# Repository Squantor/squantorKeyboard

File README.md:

# My own keyboard stuff
This repository contains my experiments on creating my own keyboard electronics and software.
## Structure
* [electronics](electronics/README.md) contains keyboard circuits boards and possible controllers.
* [software](software/README.md) contains all the software used in the project. This can be embedded, PC/smartphone or test scripts, anything a computer can execute resides here.
* [mechanical](mechanical/README.md) contains all the CAD drawings, mostly 3d printable objects.
* [documentation](documentation/index.md) contains all project documentation, logs, research, papers, datasheets and more.
## Cloning
This repository makes extensive use of submodules, use ```git clone --recurse-submodules https://github.com/Squantor/squantorKeyboard.git``` to clone everything in one go.
# TODOs
Open tasks

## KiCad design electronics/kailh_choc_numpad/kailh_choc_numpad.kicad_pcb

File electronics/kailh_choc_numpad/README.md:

# Kailh Choc numpad tryout
Trying out kailh choc numpad with using 2 port expanders
# HSI (Hardware Software Interface)
* 16 bit port expander at address 0x??
	* Pin 0: Row 0 drive
	* Pin 1: Row 1 drive
	* Pin 2: Row 2 drive
	* Pin 3: Row 2 drive
	* Pin 4: Row 2 drive
	* Pin 8: Column 0 LED drive, pulled up by 100K
	* Pin 9: Column 1 LED drive, pulled up by 100K
	* Pin 10: Column 2 LED drive, pulled up by 100K
	* Pin 11: Column 3 LED drive, pulled up by 100K
* 8 bit port expander at address 0x??
	* Pin 0: Column 0 switch sense, pulled up by 4.7K
	* Pin 1: Column 1 switch sense, pulled up by 4.7K
	* Pin 2: Column 2 switch sense, pulled up by 4.7K
	* Pin 3: Column 3 switch sense, pulled up by 4.7K
Matrix switches and definitions:
TODO
## TODO's
Still some things need to be done:
* schematic entry
* expand HSI 
* PCB layout
* Review with one night in between
* Produce at [OSHPARK](https://oshpark.com/)
* Assemble
* Test & characterise
* update Readme.md with pictures and BOM
## BOM
* TODO: 16 bit port expander
* TODO: 8 bit port expander
* TODO: Kailh choc 1350 switches
* TODO: keycaps from kailhua for kailh choc keys

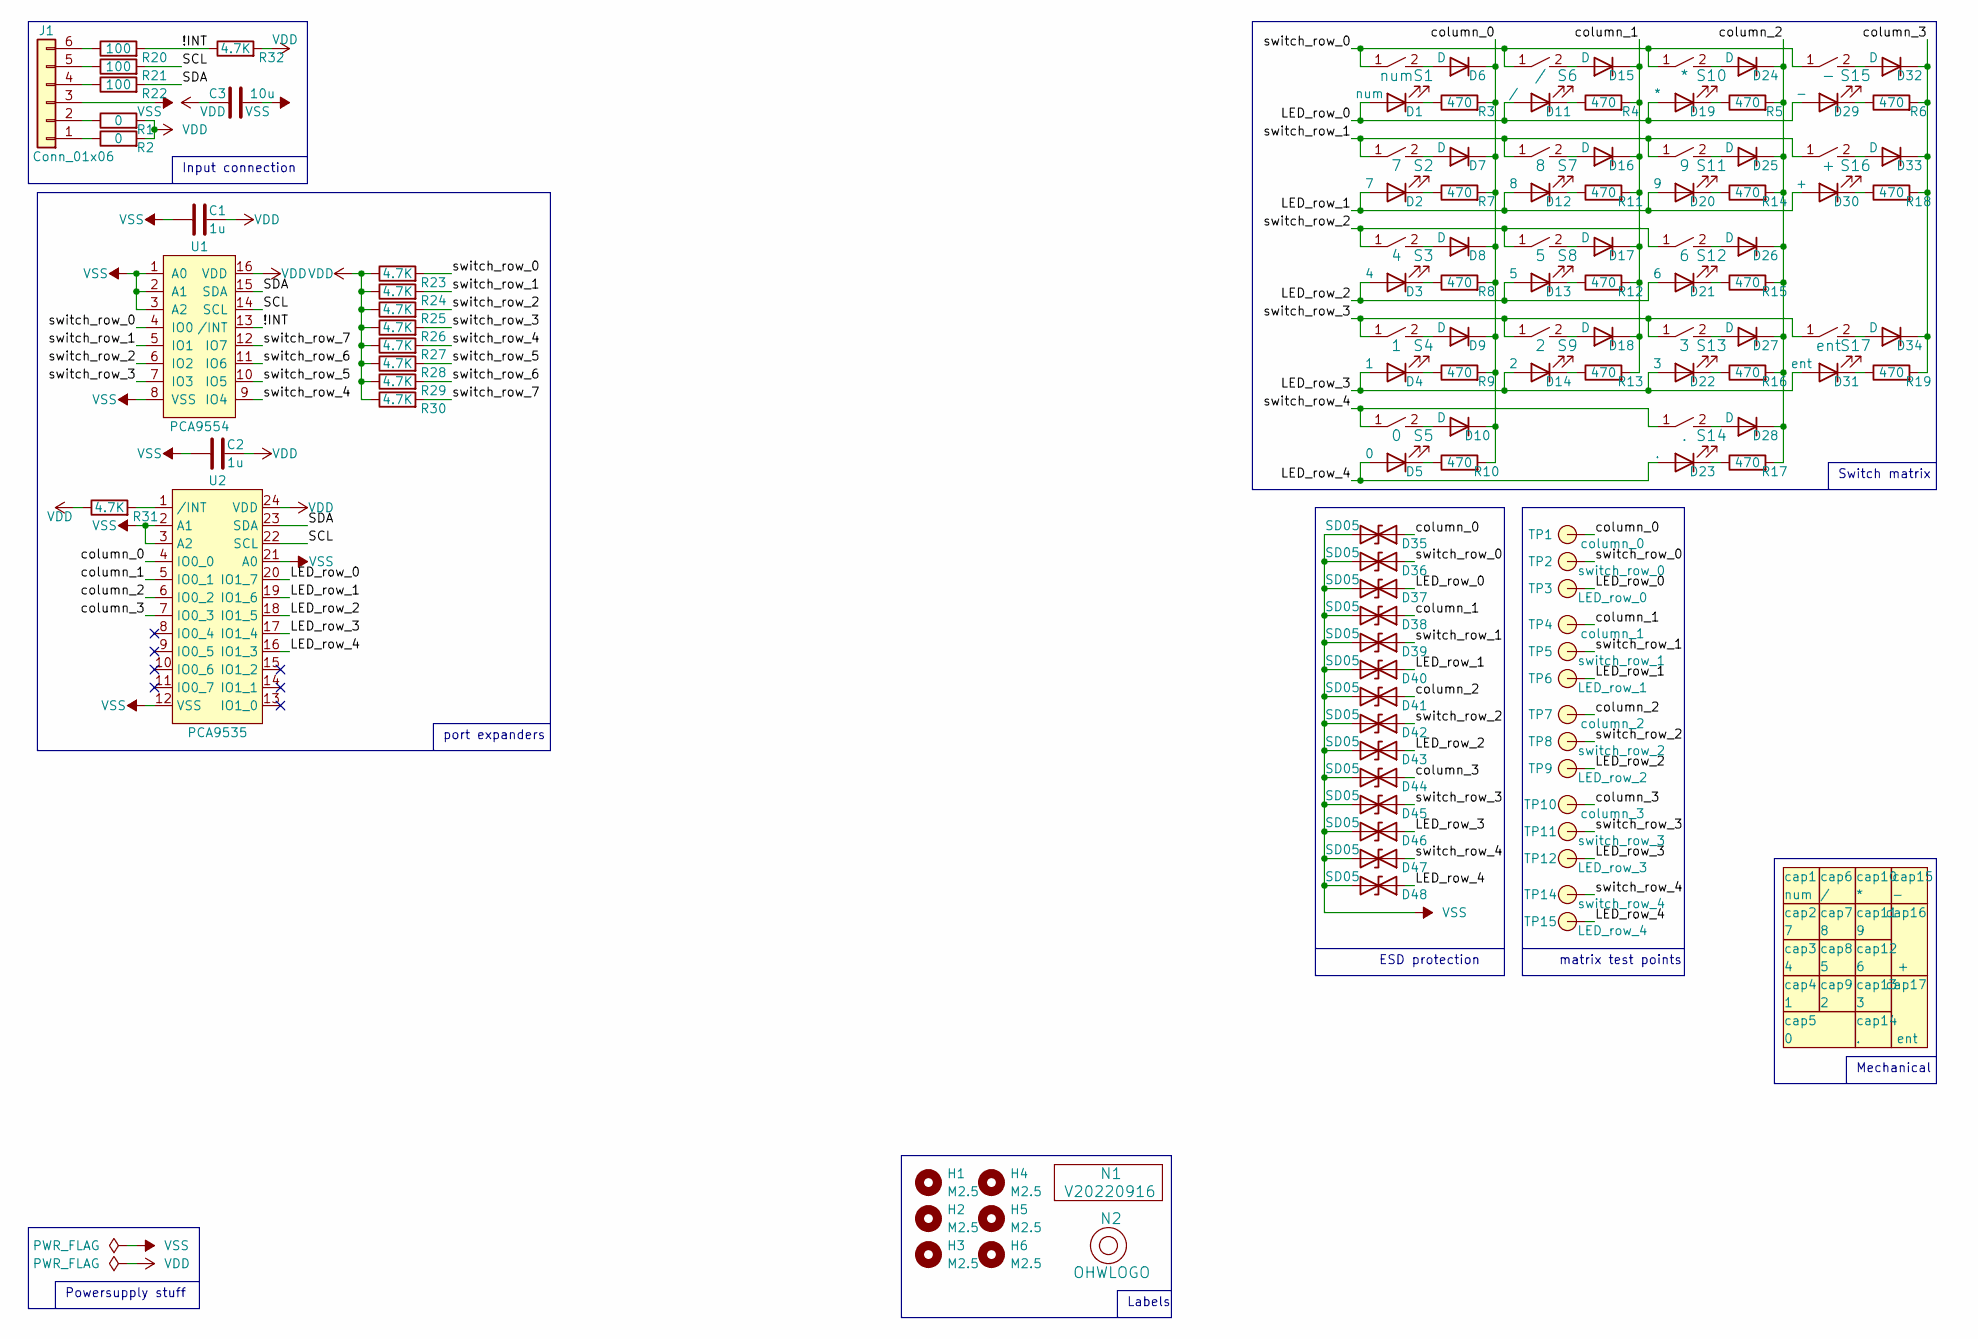
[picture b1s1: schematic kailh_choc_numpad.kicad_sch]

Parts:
C1, C2: 1u; C_0603
C3: 10u; C_0805
D1: num; LED_1208_0603
D2: 7; LED_1208_0603
D3: 4; LED_1208_0603
D4: 1; LED_1208_0603
D5: 0; LED_1208_0603
D6, D7, D8, D9, D10, D15, D16, D17, D18, D24, D25, D26, D27, D28, D32, D33, D34: D; SOD-523_hand
D11: /; LED_1208_0603
D12: 8; LED_1208_0603
D13: 5; LED_1208_0603
D14: 2; LED_1208_0603
D19: *; LED_1208_0603
D20: 9; LED_1208_0603
D21: 6; LED_1208_0603
D22: 3; LED_1208_0603
D23: .; LED_1208_0603
D29: -; LED_1208_0603
D30: +; LED_1208_0603
D31: ent; LED_1208_0603
D35, D36, D37, D38, D39, D40, D41, D42, D43, D44, D45, D46, D47, D48: SD05; D_SOD-323
H1, H2, H3, H4, H5, H6: M2.5; MountingHole_2.7mm_M2.5
J1: Conn_01x06; JST_PH_S6B-PH-K_1x06_P2.00mm_Horizontal
N1: V20220916; Label_Generic
N2: OHWLOGO; OSHW-Symbol_8.9x8mm_SilkScreen
R1, R2: 0; R_0603_hand
R3, R4, R5, R6, R7, R8, R9, R10, R11, R12, R13, R14, R15, R16, R17, R18, R19: 470; R_0603_hand
R20, R21, R22: 100; R_0603_hand
R23, R24, R25, R26, R27, R28, R29, R30, R31, R32: 4.7K; R_0603_hand
S1: num; KAILH_choc_LED
S2: 7; KAILH_choc_LED
S3: 4; KAILH_choc_LED
S4: 1; KAILH_choc_LED
S5: 0; KAILH_choc_LED
S6: /; KAILH_choc_LED
S7: 8; KAILH_choc_LED
S8: 5; KAILH_choc_LED
S9: 2; KAILH_choc_LED
S10: *; KAILH_choc_LED
S11: 9; KAILH_choc_LED
S12: 6; KAILH_choc_LED
S13: 3; KAILH_choc_LED
S14: .; KAILH_choc_LED
S15: -; KAILH_choc_LED
S16: +; KAILH_choc_LED
S17: ent; KAILH_choc_LED
TP1: column_0; TestPoint_hole_H05R10
TP2: switch_row_0; TestPoint_hole_H05R10
TP3: LED_row_0; TestPoint_hole_H05R10
TP4: column_1; TestPoint_hole_H05R10
TP5: switch_row_1; TestPoint_hole_H05R10
TP6: LED_row_1; TestPoint_hole_H05R10
TP7: column_2; TestPoint_hole_H05R10
TP8: switch_row_2; TestPoint_hole_H05R10
TP9: LED_row_2; TestPoint_hole_H05R10
TP10: column_3; TestPoint_hole_H05R10
TP11: switch_row_3; TestPoint_hole_H05R10
TP12: LED_row_3; TestPoint_hole_H05R10
TP14: switch_row_4; TestPoint_hole_H05R10
TP15: LED_row_4; TestPoint_hole_H05R10
U1: PCA9554; SOT403-1-NXP
U2: PCA9535; SOT355-1-NXP
cap1: num; KAILH_choc_keycap_1
cap2: 7; KAILH_choc_keycap_1
cap3: 4; KAILH_choc_keycap_1
cap4: 1; KAILH_choc_keycap_1
cap5: 0; KAILH_choc_keycap_2_horizontal
cap6: /; KAILH_choc_keycap_1
cap7: 8; KAILH_choc_keycap_1
cap8: 5; KAILH_choc_keycap_1
cap9: 2; KAILH_choc_keycap_1
cap10: *; KAILH_choc_keycap_1
cap11: 9; KAILH_choc_keycap_1
cap12: 6; KAILH_choc_keycap_1
cap13: 3; KAILH_choc_keycap_1
cap14: .; KAILH_choc_keycap_1
cap15: -; KAILH_choc_keycap_1
cap16: +; KAILH_choc_keycap_2_vertical
cap17: ent; KAILH_choc_keycap_2_vertical

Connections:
/!INT: R20.2, R32.1, U1.13 (/INT)
/LED_row_0: D1.2 (A), D11.2 (A), D19.2 (A), D29.2 (A), D37.1 (A1), TP3.1, U2.20 (IO1_7)
/LED_row_1: D2.2 (A), D12.2 (A), D20.2 (A), D30.2 (A), D40.1 (A1), TP6.1, U2.19 (IO1_6)
/LED_row_2: D3.2 (A), D13.2 (A), D21.2 (A), D43.1 (A1), TP9.1, U2.18 (IO1_5)
/LED_row_3: D4.2 (A), D14.2 (A), D22.2 (A), D31.2 (A), D46.1 (A1), TP12.1, U2.17 (IO1_4)
/LED_row_4: D5.2 (A), D23.2 (A), D48.1 (A1), TP15.1, U2.16 (IO1_3)
/SCL: R21.2, U1.14 (SCL), U2.22 (SCL)
/SDA: R22.2, U1.15 (SDA), U2.23 (SDA)
/column_0: D6.1 (K), D7.1 (K), D8.1 (K), D9.1 (K), D10.1 (K), D35.1 (A1), R3.2, R7.2, R8.2, R9.2, R10.2, TP1.1, U2.4 (IO0_0)
/column_1: D15.1 (K), D16.1 (K), D17.1 (K), D18.1 (K), D38.1 (A1), R4.2, R11.2, R12.2, R13.2, TP4.1, U2.5 (IO0_1)
/column_2: D24.1 (K), D25.1 (K), D26.1 (K), D27.1 (K), D28.1 (K), D41.1 (A1), R5.2, R14.2, R15.2, R16.2, R17.2, TP7.1, U2.6 (IO0_2)
/column_3: D32.1 (K), D33.1 (K), D34.1 (K), D44.1 (A1), R6.2, R18.2, R19.2, TP10.1, U2.7 (IO0_3)
/switch_row_0: D36.1 (A1), R23.2, S1.1, S6.1, S10.1, S15.1, TP2.1, U1.4 (IO0)
/switch_row_1: D39.1 (A1), R24.2, S2.1, S7.1, S11.1, S16.1, TP5.1, U1.5 (IO1)
/switch_row_2: D42.1 (A1), R25.2, S3.1, S8.1, S12.1, TP8.1, U1.6 (IO2)
/switch_row_3: D45.1 (A1), R26.2, S4.1, S9.1, S13.1, S17.1, TP11.1, U1.7 (IO3)
/switch_row_4: D47.1 (A1), R27.2, S5.1, S14.1, TP14.1, U1.9 (IO4)
/switch_row_5: R28.2, U1.10 (IO5)
/switch_row_6: R29.2, U1.11 (IO6)
/switch_row_7: R30.2, U1.12 (IO7)
unnamed: D1.1 (K), R3.1
unnamed: D2.1 (K), R7.1
unnamed: D3.1 (K), R8.1
unnamed: D4.1 (K), R9.1
unnamed: D5.1 (K), R10.1
unnamed: D6.2 (A), S1.2
unnamed: D7.2 (A), S2.2
unnamed: D8.2 (A), S3.2
unnamed: D9.2 (A), S4.2
unnamed: D10.2 (A), S5.2
unnamed: D11.1 (K), R4.1
unnamed: D12.1 (K), R11.1
unnamed: D13.1 (K), R12.1
unnamed: D14.1 (K), R13.1
unnamed: D15.2 (A), S6.2
unnamed: D16.2 (A), S7.2
unnamed: D17.2 (A), S8.2
unnamed: D18.2 (A), S9.2
unnamed: D19.1 (K), R5.1
unnamed: D20.1 (K), R14.1
unnamed: D21.1 (K), R15.1
unnamed: D22.1 (K), R16.1
unnamed: D23.1 (K), R17.1
unnamed: D24.2 (A), S10.2
unnamed: D25.2 (A), S11.2
unnamed: D26.2 (A), S12.2
unnamed: D27.2 (A), S13.2
unnamed: D28.2 (A), S14.2
unnamed: D29.1 (K), R6.1
unnamed: D30.1 (K), R18.1
unnamed: D31.1 (K), R19.1
unnamed: D32.2 (A), S15.2
unnamed: D33.2 (A), S16.2
unnamed: D34.2 (A), S17.2
unnamed: J1.1, R2.1
unnamed: J1.2, R1.1
unnamed: J1.4, R22.1
unnamed: J1.5, R21.1
unnamed: J1.6, R20.1
unnamed: R31.2, U2.1 (/INT)
VDD: C1.2, C2.2, C3.1, R1.2, R2.2, R23.1, R24.1, R25.1, R26.1, R27.1, R28.1, R29.1, R30.1, R31.1, R32.2, U1.16 (VDD), U2.24 (VDD)
VSS: C1.1, C2.1, C3.2, D35.2 (A2), D36.2 (A2), D37.2 (A2), D38.2 (A2), D39.2 (A2), D40.2 (A2), D41.2 (A2), D42.2 (A2), D43.2 (A2), D44.2 (A2), D45.2 (A2), D46.2 (A2), D47.2 (A2), D48.2 (A2), J1.3, U1.1 (A0), U1.2 (A1), U1.3 (A2), U1.8 (VSS), U2.2 (A1), U2.3 (A2), U2.12 (VSS), U2.21 (A0)

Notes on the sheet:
Labels
Switch matrix
matrix test points
port expanders
Powersupply stuff
Mechanical
Input connection
ESD protection

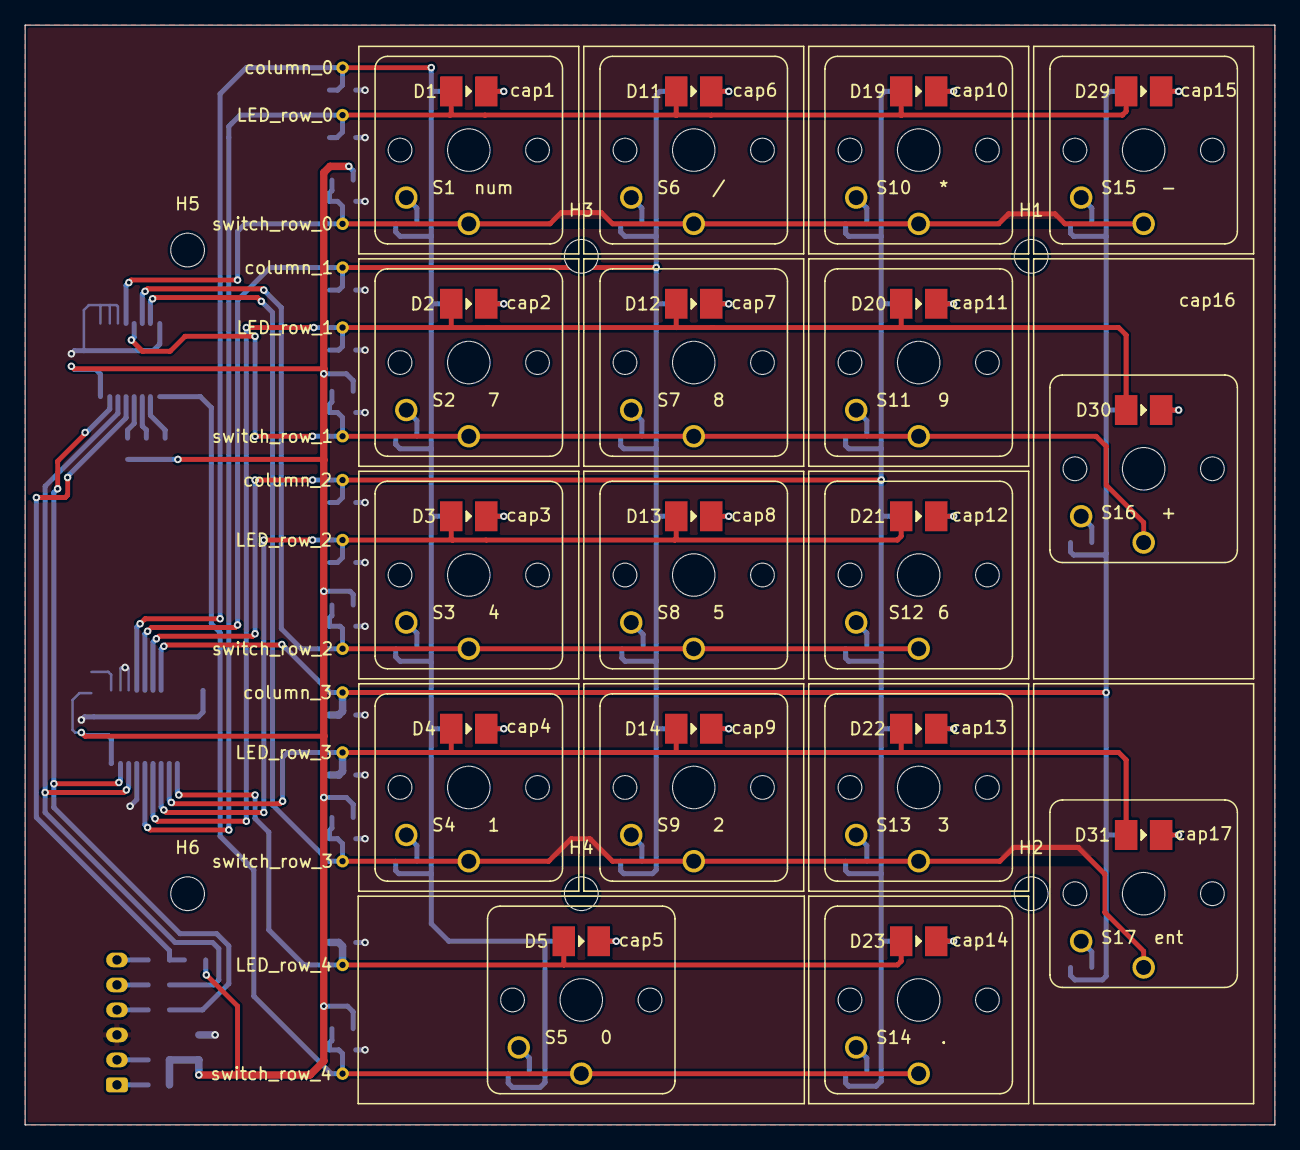
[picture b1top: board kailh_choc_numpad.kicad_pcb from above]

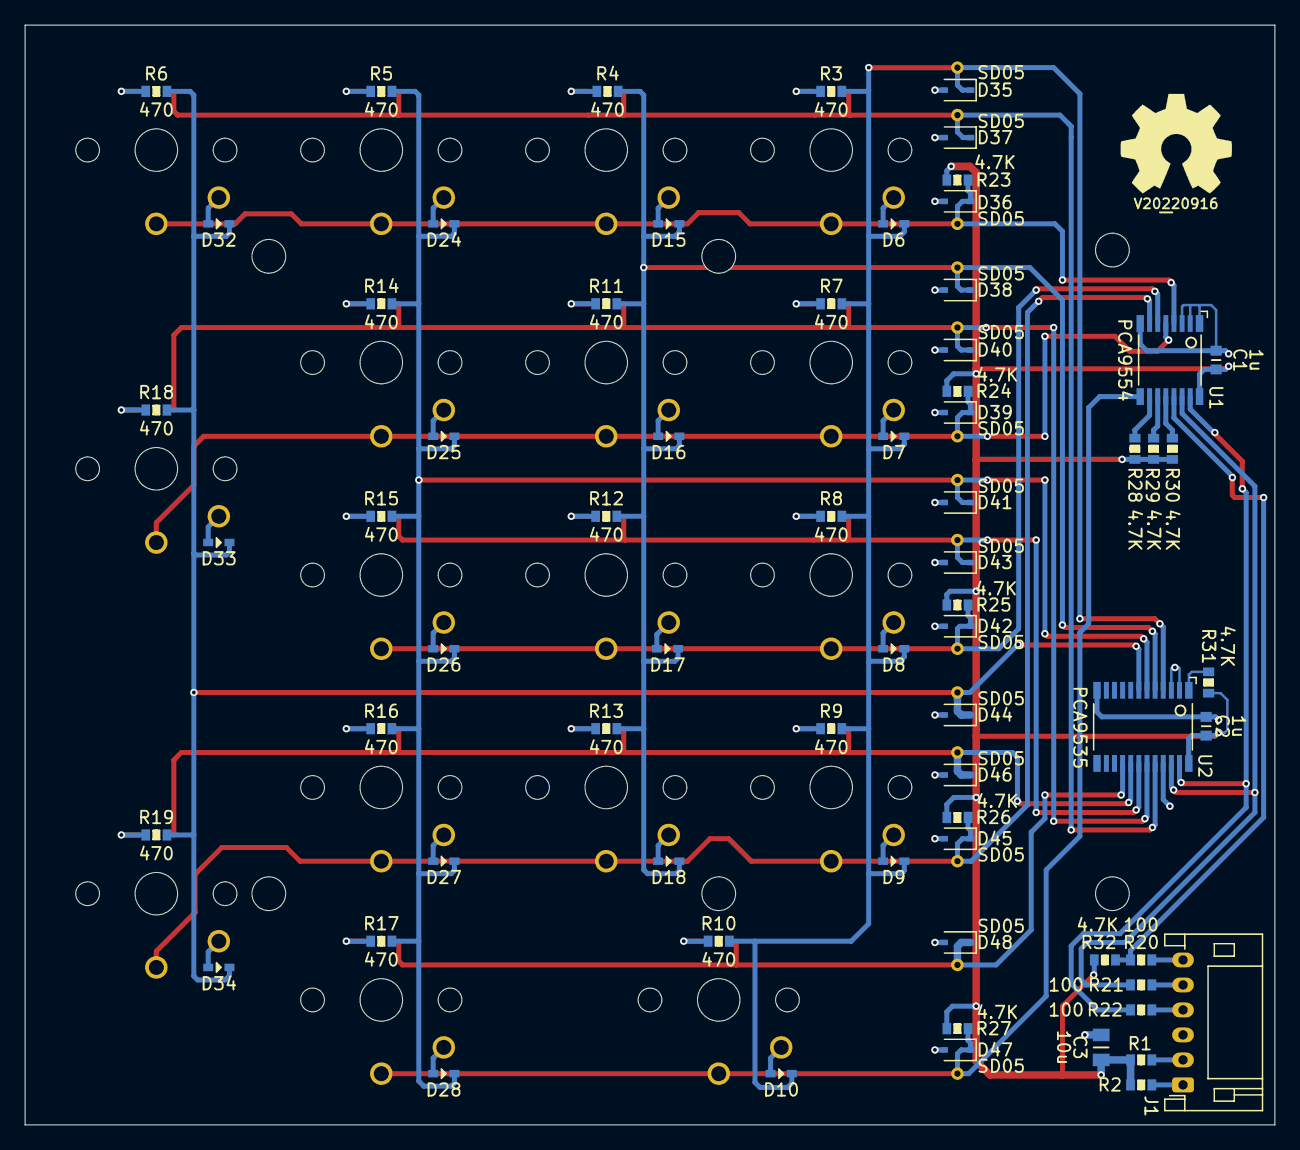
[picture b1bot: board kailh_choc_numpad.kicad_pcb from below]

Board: 2 copper layers, 100.0 x 88.0 mm, 142 parts (71 on the bottom side), 62 nets.

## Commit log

2022-02-23 initial creation of project
2022-02-23 started with left side of a split ortholinear keyboard
2022-02-23 changed file layout
2022-02-23 minor changes
2022-02-24 parking split ortho left, starting with a more grid layout
2022-02-24 updated plate thicknesses and removed borders
2022-02-24 further mechanical changes to switch plate
2022-06-24 first beginning of kailh choc numpad
2022-06-24 added cutouts for switch clips
2022-06-24 not mirrored now
2022-06-24 WIP: choc numpads
2022-06-25 adjusted dimensions to better fit
2022-06-26 WIP: adjusting stabilizer holes, again
2022-06-26 added pcb library submodule
2022-06-26 started with kailh choc numpad
2022-06-26 finally got the stabilizer positions and thicknesses correct
2022-06-26 fixed error with footprint table dirs and updated library
2022-06-26 fine tuned dimensions for stabilizers
2022-06-26 placed keycaps
2022-06-26 Added another kicad temporary
2022-06-26 minor adjustments
2022-06-26 placing and routing keyboard matrix
2022-06-26 fully placed and routed switch matrix
2022-06-26 updated diode 3d models
2022-06-26 added, placed and routed ESD diodes
2022-07-14 Updated PCB library
2022-07-14 added LED resistors
2022-07-14 placed resistors, now routing needed
2022-07-15 removed transient settings file
2022-07-15 placed and routed LED resistors
2022-07-15 added i2c port expander but wrong footprint, now
2022-07-16 added I2C port expanders
2022-07-16 imported I2C expanders, time to route
2022-07-16 added new port expanders
2022-07-17 further placing and routing
2022-07-18 routed all traces
2022-07-18 newer submodule
2022-07-18 saving small changes
2022-08-24 silk placement completed
2022-08-24 fixed via sizes
2022-08-24 updated broken IC footprint, added OHW logo
2022-09-16 added mounting holes
